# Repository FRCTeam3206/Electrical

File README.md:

# Electrical
Container for Electrical team.  Includes to-do, issues, shopping, coordination and communication.
Location for Arduino code for 80/20 bots and Zumos.

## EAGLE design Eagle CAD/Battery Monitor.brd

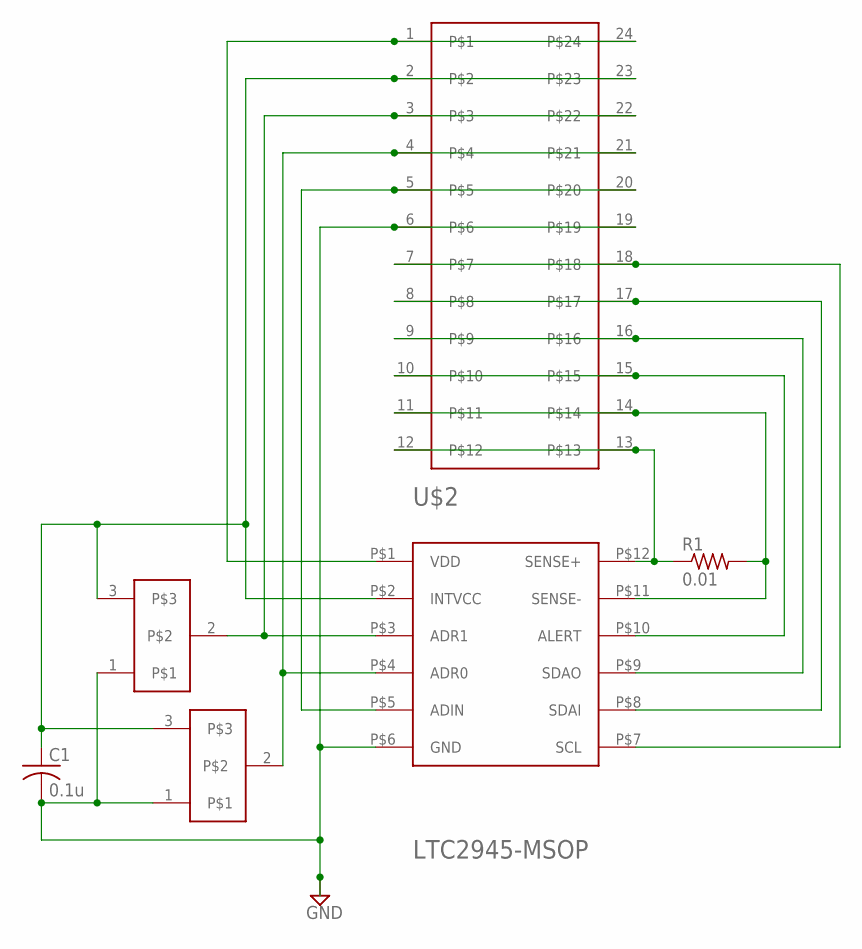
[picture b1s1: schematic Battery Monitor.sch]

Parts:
C1: 0.1u; C1812
R1: 0.01; R2010
U$2: LTC2945-MSOP; MSOP12
U$3: 24-PINEVAL; DIL24-6
U$4, U$5: JUMP-3

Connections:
GND: C1.2, U$2.P$6 (GND), U$3.6, U$3.19, U$4.1, U$5.1
unnamed: C1.1, U$2.P$2 (INTVCC), U$3.2, U$3.23, U$4.3, U$5.3
unnamed: U$2.P$1 (VDD), U$3.1, U$3.24
unnamed: U$2.P$3 (ADR1), U$3.3, U$3.22, U$4.2
unnamed: U$2.P$4 (ADR0), U$3.4, U$3.21, U$5.2
unnamed: U$2.P$5 (ADIN), U$3.5, U$3.20
unnamed: U$2.P$7 (SCL), U$3.7, U$3.18
unnamed: U$2.P$9 (SDAO), U$3.9, U$3.16
unnamed: R1.1, U$2.P$12 (SENSE+), U$3.12, U$3.13
unnamed: U$2.P$10 (ALERT), U$3.10, U$3.15
unnamed: R1.2, U$2.P$11 (SENSE-), U$3.11, U$3.14
unnamed: U$2.P$8 (SDAI), U$3.8, U$3.17

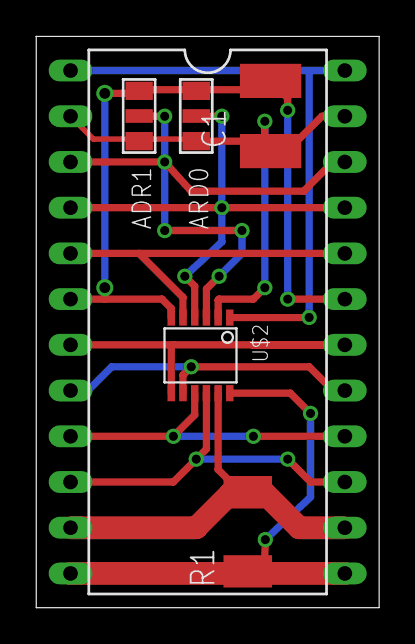
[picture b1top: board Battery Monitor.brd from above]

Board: 2 copper layers, 19.0 x 31.8 mm, 6 parts (0 on the bottom side), 12 nets.

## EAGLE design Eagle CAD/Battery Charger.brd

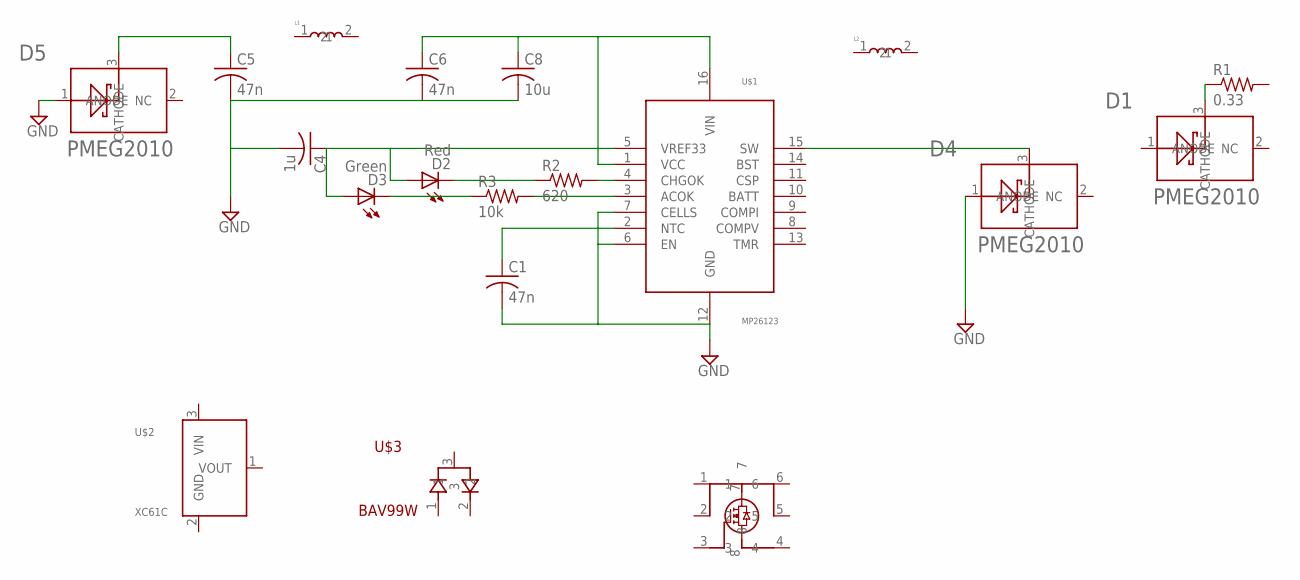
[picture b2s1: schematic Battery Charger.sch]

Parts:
C1, C5, C6: 47n; C0805
C4: 1u; C0805
C8: 10u; C0805
D1, D4, D5: DIODE-PMEG2010; DIODE-SOT23
D2: Red; LED3MM
D3: Green; LED3MM
L1, L2: L-SMD-2; SMD-2
Q1: MOSFET-IRFHS8242; PQFN2X2
R1: 0.33; R2512
R2: 620; R0805
R3: 10k; R0805
U$1: IC-MP26123; QFN16-4MM
U$2: IC-XC61C; SOT23
U$3: DIODE-BAV99W; SOT323

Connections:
1: Q1.1
2: Q1.2
4: Q1.4
5: Q1.5
6: Q1.6
7: Q1.7
8: Q1.8
GND: C1.2, C4.2, C5.2, C6.2, C8.2, D4.1 (ANODE), D5.1 (ANODE), U$1.6 (EN), U$1.7 (CELLS), U$1.12 (GND)
unnamed: R2.2, U$1.4 (CHGOK)
unnamed: R3.2, U$1.3 (ACOK)
unnamed: C4.1, D2.A, D3.A, U$1.5 (VREF33)
unnamed: C6.1, C8.1, U$1.1 (VCC), U$1.16 (VIN)
unnamed: C5.1, D5.3 (CATHODE)
unnamed: D2.K (C), R2.1
unnamed: D3.K (C), R3.1
unnamed: C1.1, U$1.2 (NTC)
unnamed: D4.3 (CATHODE), U$1.15 (SW)
unnamed: D1.3 (CATHODE), R1.1

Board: 2 copper layers, 19 parts (0 on the bottom side), 11 nets, no tracks yet.

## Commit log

2016-11-11 Add files via upload
    Initial archive.
2016-11-11 Added comments
2016-11-11 Added more comments.
    Confirmed more significant changes required to make this work with with
    Zumobot.
2016-11-11 Initial archive.
2016-11-11 Changed CS pin
    Modified hardware and changed CS pin to 6 in SW. Added documentation.
2016-11-15 Initial archive
    Playing notes works. Includes rests and For loop.
2016-11-15 Merge remote-tracking branch 'refs/remotes/origin/master' into Raj-Gandhi
    # Conflicts:
    # Eval_Zumo_Speaker/Eval_Zumo_Speaker.ino
2016-11-15 Fixed merge conflict.
2016-11-15 Initial archive
2016-11-15 Functional
    This functional but mostly example code. The program reads Vbat and
    beeps back the voltage. There's a quick two beep to ack. Then one beep
    per volt then, at a higher pitch, one beep per tenth of a volt. The
    intent is to play warning beep message when Vbat is too low in order to
    conserve LiIon batteries.
2016-11-15 Initial archive.
    Base code.
2016-11-15 Added Vbat tones
    Zumo button press emits tones that correlate to Vbat.
2016-11-16 Tidy code
    Moved Vbat tones to functions.
2016-11-24 Added Eagle CAD (PC board) files.
2016-12-14 Finalized.
2016-12-14 Lasers are working.
2017-01-17 Renamed
2017-01-17 Initial archive
    Controls motor speed by potentiometer.
2017-01-28 Minor update
2017-02-23 Remove the project from FRC3206
    Move to Raj's local.
2017-06-03 Low Battery Detect
    Working on implementation of low battery detection.
2018-03-14 Tweaks. Working
2018-04-23 Fixed RC controller
    Swapped throttle and steering inputs. Added RSL feature (health blink)
    on pin 13 LED.
2018-04-26 Working on combining manual and auto Vbat level check.
2018-04-26 Cleaned checkBattery
2018-07-23 Functional
    Tweaked values.
2018-08-27 Refactored Throttle and Steering calculations
    Added accel limit with IIR filter for Throttle. Removed some Deadband
    because not needed. Scaled Steering so steering isn't as sensitve. The
    change should make it easier to drive without tipping. Some risk that
    there's an accidental decrease in max speed.
2018-12-06 New Pistol Grip Code
    This code allows Pistol Grip RC remotes to be used with a tank drive
    robot.
2018-12-08 Change from degrees to uS
2018-12-08 Finished implementation of throttle and steering smoothing
2018-12-14 Made improvements to stability
2018-12-18 Ready for extended testing.
    Code is tested and generally functional. Further improvements would
    require hardware changes.
2019-01-29 Added intake to Blinky Mecanum
2019-09-12 Sync to GitHub
2019-09-15 Fixed steering implemented aux pin
    Changed steering pin
    made accel limited dependant on aux button
2019-09-30 Added Blinking light
    When in normal mode, light blinks normally, once button is pressed light blinks faster
2019-10-12 Create WiringDiagrams
2019-10-14 intial archive
2019-10-15 added states
    example auton code
2019-11-19 Introduce small step delays
    Rather than delaying in switch statement for each STATE, make each
    "state" a function that returns whether or not it is currently
    "running" based on elapsed time. If a state function returns 0, call a
    function to set the next state and reset the elapsed timer. End with
    stopped bot, ready for teleop.
2021-11-02 First commit for simple RC code
2021-11-02 Initial upload of ReadMe.adoc
2021-11-02 Move Simple_RC_PistolGrip to proper folder
2021-11-07 Update Simple_RC_PistolGrip.ino
    - Added code to convert RC inputs to motor outputs
    - Separated debugging output code into function debug_output
    - debug_output accepts can show either the input or output values
2021-11-09 Improve debug_output() performance
    debug_output() only writes when there is space in the buffer
2021-11-21 now checks for no signal from controller
2021-12-05 Add debug output delay to improve readability in terminal
2021-12-05 Removed timeout setting from input pulseIn()
2021-12-05 Fixed debug delay logic
2021-12-07 Base dbg_delay on the current millis()
2021-12-07 First commit of Simple_RC_Tank
2021-12-07 Fixed stray negative sign
2021-12-07 Slow debug output
2021-12-07 Increase DBG_DELAY to slow debug output
2024-01-12 Neopixel-length-finder files added
